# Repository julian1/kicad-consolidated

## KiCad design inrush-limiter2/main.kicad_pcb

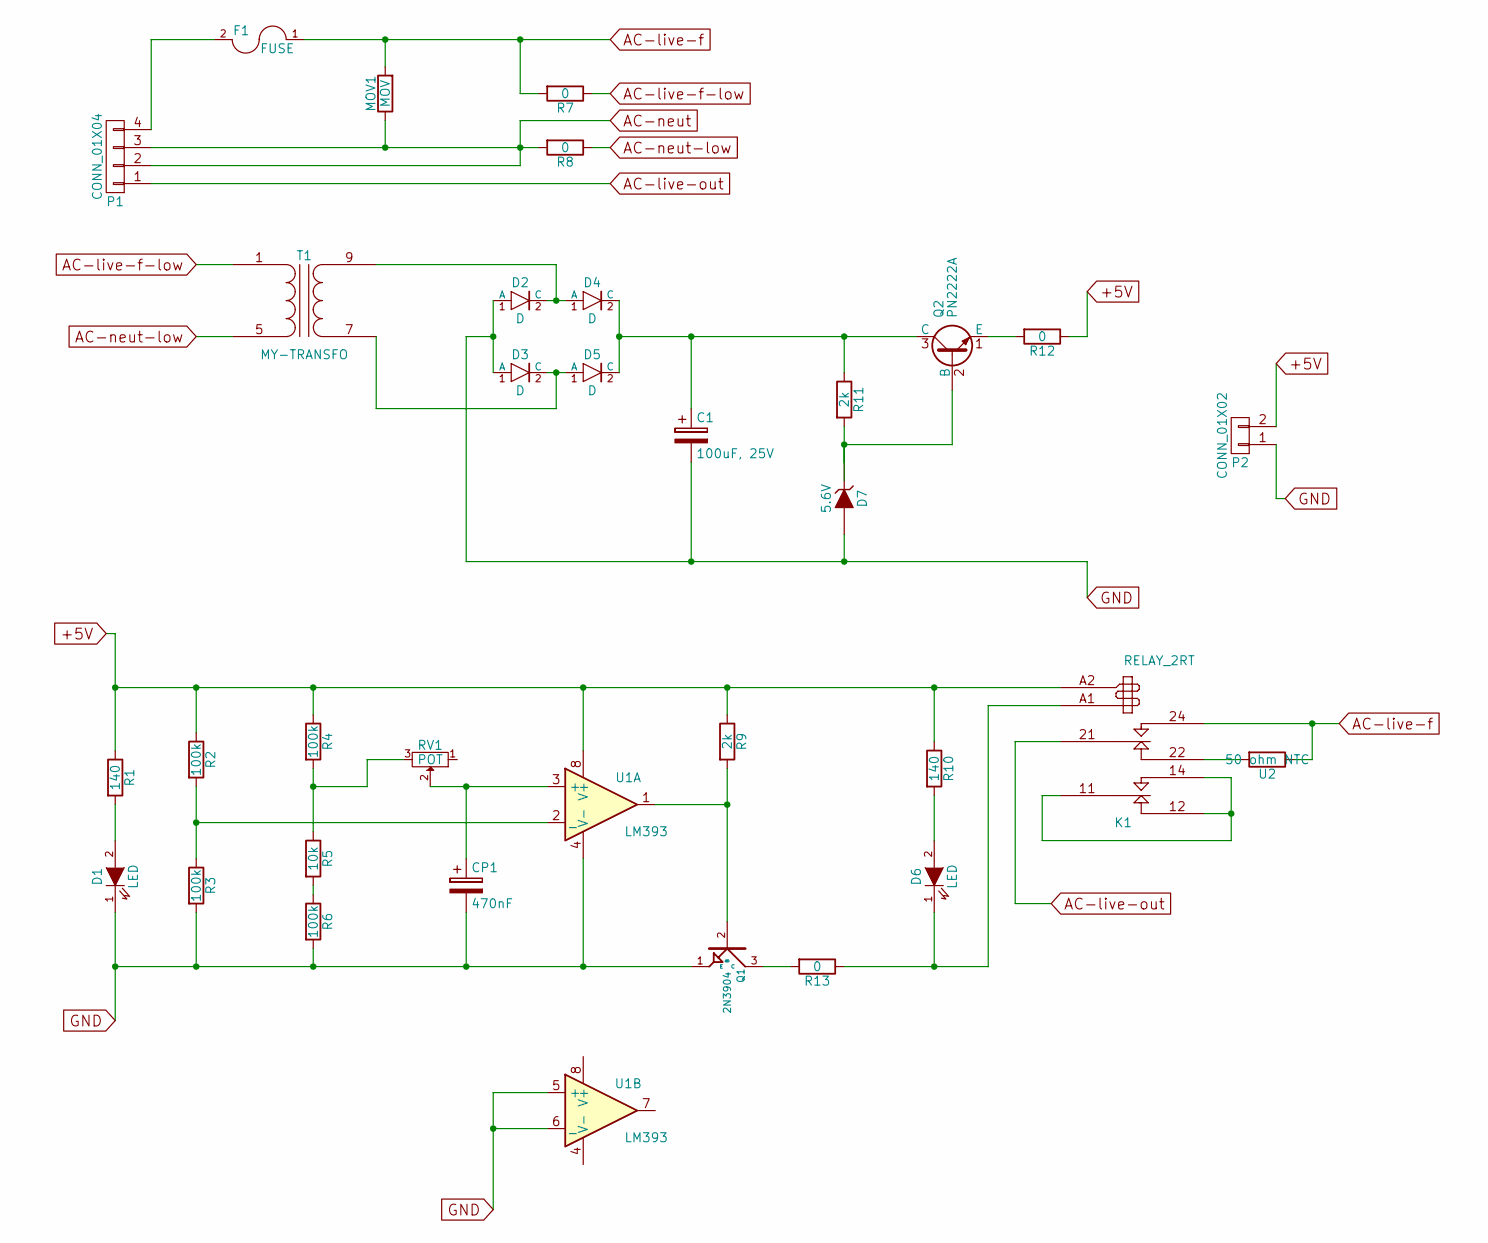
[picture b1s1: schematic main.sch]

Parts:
C1: 100uF, 25V; C_Radial_D8_L13_P3.8
CP1: 470nF; C_Rect_L7_W3.5_P5
D1, D6: LED; LED-5MM
D2, D3, D4, D5: D; Diode_DO-35_SOD27_Horizontal_RM10
D7: 5.6V; Diode_DO-35_SOD27_Horizontal_RM10
F1: FUSE; Fuseholder5x20_horiz_SemiClosed_Casing10x25mm
K1: RELAY_2RT; Relay_DPDT_Schrack-RT2_RM5mm
MOV1: MOV; Resistor_Horizontal_RM10mm
P1: CONN_01X04; fuck
P2: CONN_01X02; Pin_Header_Straight_1x02
Q1: 2N3904; TO-92_Inline_Wide
Q2: PN2222A; TO-92_Inline_Wide
R1, R10: 140; Resistor_Horizontal_RM7mm
R2, R3, R4, R6: 100k; Resistor_Horizontal_RM7mm
R5: 10k; Resistor_Horizontal_RM7mm
R7, R8, R12, R13: 0; Resistor_Horizontal_RM7mm
R9, R11: 2k; Resistor_Horizontal_RM7mm
RV1: POT; Potentiometer_Bourns_3296W_3-8Zoll_Inline_ScrewUp
T1: MY-TRANSFO; my-transformer
U1: LM393; DIP-8_W7.62mm
U2: 50 ohm NTC; Resistor_Horizontal_RM10mm

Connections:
+5V: K1.A2 (9), P2.2, R1.1, R2.1, R4.1, R9.1, R10.1, R12.1, U1.8 (V+)
AC-live-f: F1.1, K1.24 (T1), MOV1.2, R7.2, U2.1
AC-live-f-low: R7.1, T1.1 (AA)
AC-live-out: K1.21 (C1), P1.1
AC-neut: MOV1.1, P1.2, P1.3, R8.2
AC-neut-low: R8.1, T1.5 (AB)
GND: C1.2, CP1.2, D1.1 (K), D2.1 (A), D3.1 (A), D7.2 (A), P2.1, Q1.1 (E), R3.2, R6.2, U1.4 (V-), U1.5 (+), U1.6 (_)
unnamed: C1.1, D4.2 (C), D5.2 (C), Q2.3 (C), R11.1
unnamed: CP1.1, RV1.2, U1.3 (+)
unnamed: D1.2 (A), R1.2
unnamed: D2.2 (C), D4.1 (A), T1.9 (SB)
unnamed: D3.2 (C), D5.1 (A), T1.7 (SA)
unnamed: D6.1 (K), K1.A1 (8), R13.1
unnamed: D6.2 (A), R10.2
unnamed: D7.1 (K), Q2.2 (B), R11.2
unnamed: F1.2, P1.4
unnamed: K1.11 (C2), K1.12, K1.14 (T2)
unnamed: K1.22 (R1), U2.2
unnamed: Q1.2 (B), R9.2, U1.1
unnamed: Q1.3 (C), R13.2
unnamed: Q2.1 (E), R12.2
unnamed: R2.2, R3.1, U1.2 (_)
unnamed: R4.2, R5.1, RV1.3
unnamed: R5.2, R6.1

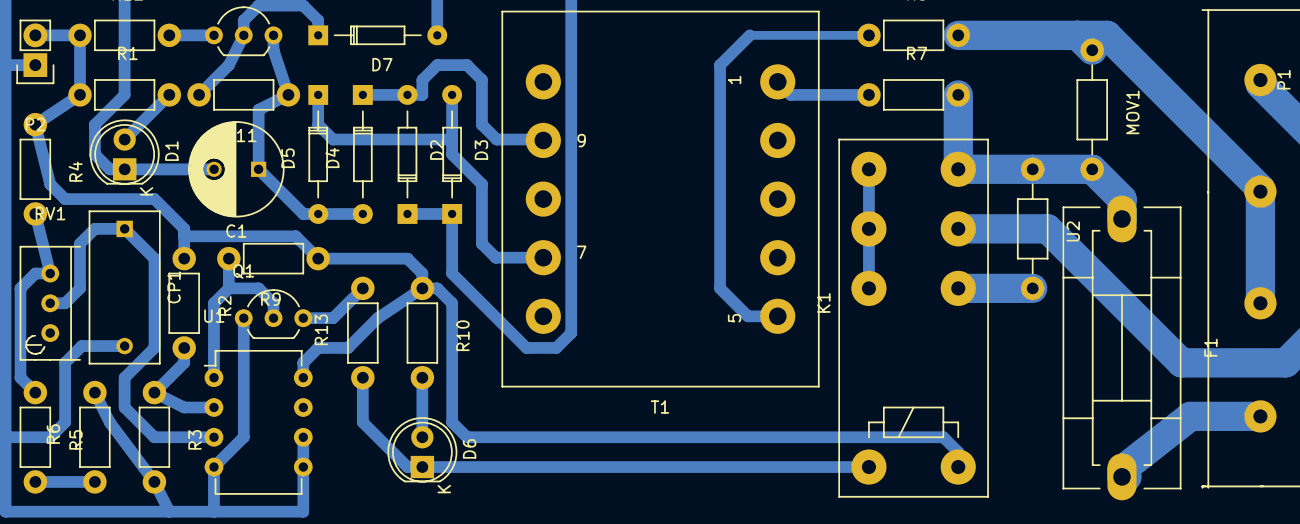
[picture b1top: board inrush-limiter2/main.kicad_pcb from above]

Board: 2 copper layers, 33 parts (0 on the bottom side), 24 nets.

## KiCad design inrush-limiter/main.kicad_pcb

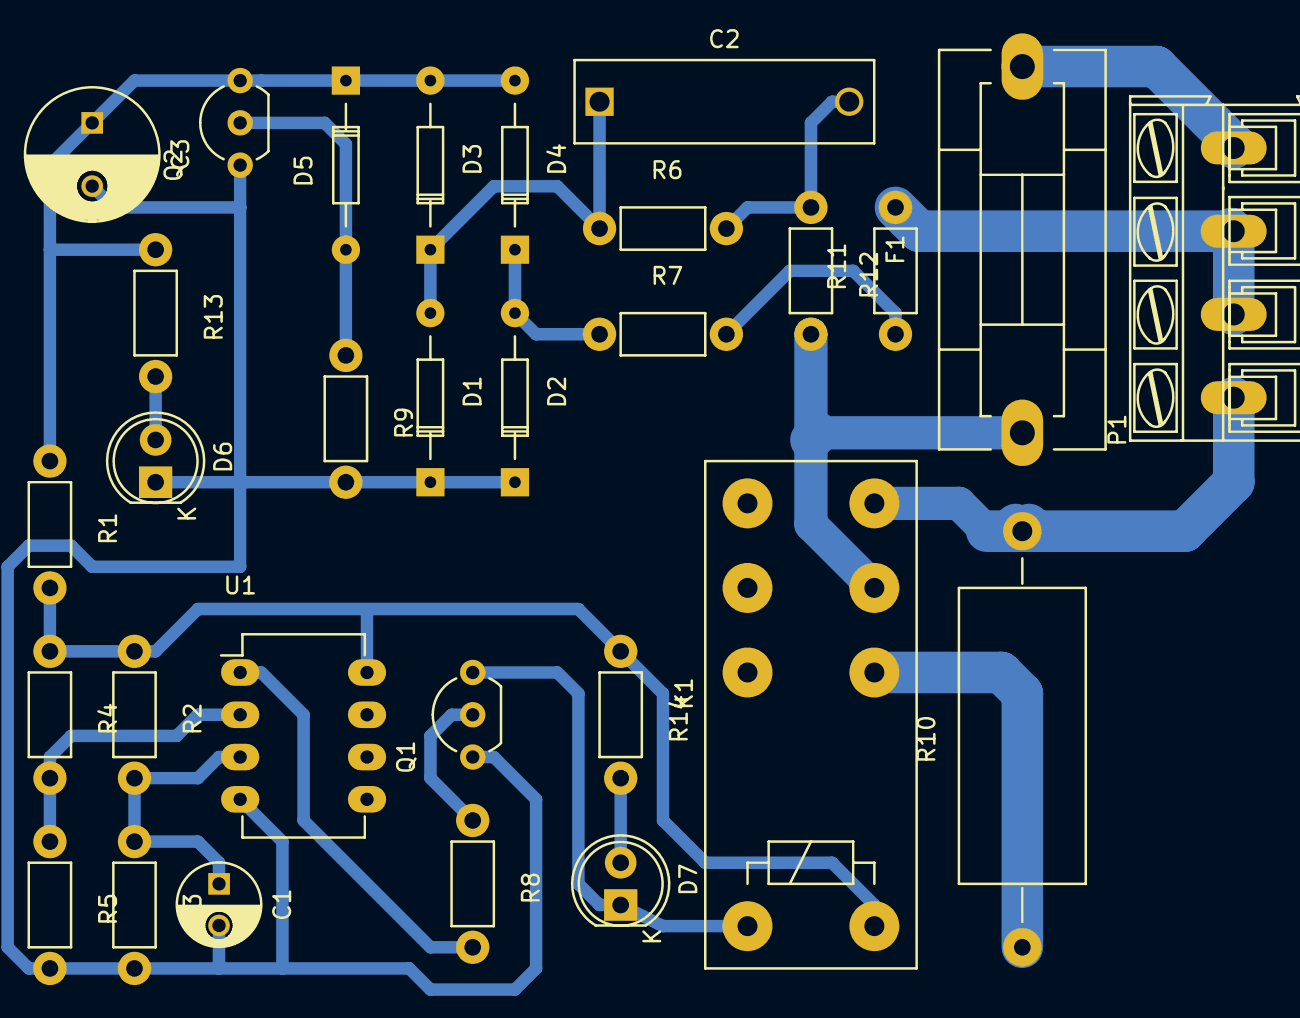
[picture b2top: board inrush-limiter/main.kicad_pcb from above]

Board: 2 copper layers, 30 parts (0 on the bottom side), 20 nets.

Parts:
C1: 3.3uF; C_Radial_D5_L6_P2.5
C2: 47nF, x2; C_Rect_L18_W5_P15
C3: 100uF, 25V; C_Radial_D8_L13_P3.8
D1, D2, D3, D4: D; Diode_DO-35_SOD27_Horizontal_RM10
D5: ZENER; Diode_DO-35_SOD27_Horizontal_RM10
D6, D7: LED; LED-5MM
F1: FUSE; Fuseholder5x20_horiz_SemiClosed_Casing10x25mm
K1: RELAY_2RT; Relay_DPDT_Schrack-RT2_RM5mm
P1: CONN_01X04; AK300-4
Q1, Q2: PN2222A; TO-92_Inline_Wide
R1, R11, R12: 0; Resistor_Horizontal_RM7mm
R2: 100K; Resistor_Horizontal_RM7mm
R3: 1M; Resistor_Horizontal_RM7mm
R4: 10K; Resistor_Horizontal_RM7mm
R5: 50K; Resistor_Horizontal_RM7mm
R6: 470k; Resistor_Horizontal_RM7mm
R7: 100; Resistor_Horizontal_RM7mm
R8: 1K; Resistor_Horizontal_RM7mm
R9: 2k; Resistor_Horizontal_RM7mm
R10: 100, 5W; Resistor_Horizontal_RM25mm
R13, R14: 140; Resistor_Horizontal_RM7mm
U1: LM393; DIP-8_W7.62mm_LongPads

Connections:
+5V: C3.1, D3.2, D4.2, D5.1, Q2.3, R1.1, R13.1
AC-live-f: F1.1, K1.21, R12.2
AC-live-f-low: C2.2, R6.2, R12.1
AC-live-out: K1.24, P1.1, R10.2
AC-neut: P1.2, P1.3, R11.2
AC-neut-low: R7.2, R11.1
GND: C1.2, C3.2, D1.1, D2.1, D6.1, Q1.1, Q2.1, R3.2, R5.2, R9.2, U1.4
unnamed: C1.1, R2.2, R3.1, U1.3
unnamed: C2.1, D1.2, D3.1, R6.1
unnamed: D2.2, D4.1, R7.1
unnamed: D5.2, Q2.2, R9.1
unnamed: D6.2, R13.2
unnamed: D7.1, K1.A1, Q1.3
unnamed: D7.2, R14.2
unnamed: F1.2, P1.4
unnamed: K1.22, R10.1
unnamed: K1.A2, R1.2, R2.1, R4.1, R14.1, U1.8
unnamed: Q1.2, R8.1
unnamed: R4.2, R5.1, U1.2
unnamed: R8.2, U1.1

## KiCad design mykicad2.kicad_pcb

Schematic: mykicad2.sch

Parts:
D1, D2: 1N4148; MiniMELF_Standard
P1: CONN_01X06; Pin_Header_Straight_1x06
Q1: MMBT3904; SOT-23
Q2: MMBT3906; SOT-23
Q3: IRF9540N; TO-220
R1, R2, R3, R4, R5: R; R_1206

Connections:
GND: P1.2, Q2.3, R2.2
unnamed: D1.1, Q1.1, R1.2
unnamed: D1.2, D2.1, P1.3
unnamed: D2.2, Q2.1, R2.1
unnamed: P1.4, Q3.3
unnamed: Q1.2, R3.1
unnamed: Q2.2, R4.2
unnamed: Q3.1, R5.1
unnamed: R3.2, R4.1, R5.2
VDD: P1.1, Q1.3, Q3.2, R1.1

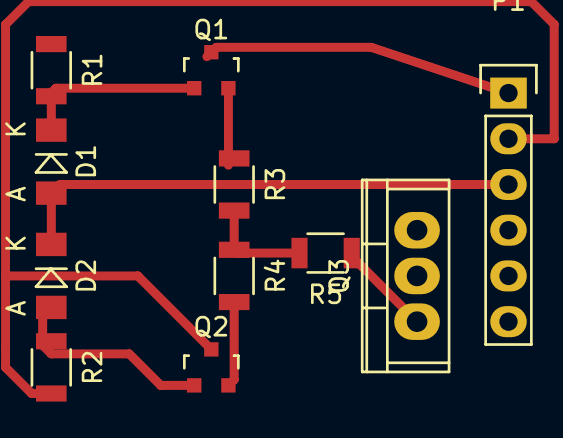
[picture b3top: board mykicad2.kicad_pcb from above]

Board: 2 copper layers, 11 parts (0 on the bottom side), 10 nets.

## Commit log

2016-08-13 orientate components
2016-08-13 vertical header pins
2016-08-13 added traces
2016-08-13 added fill
2016-08-13 fix trace
2016-08-13 improve traces
2016-08-13 big current
2016-08-13 relayout with mosfet
2016-08-14 add mosfet update traces
2016-08-26 move mosfet to separate example
2016-08-26 inrush initial
2016-08-27 looks ok
2016-08-27 add isolation resistor
2016-08-27 tidy
2016-08-27 start of pcb
2016-08-27 half-laid out
2016-08-27 fix relay footprint and reimport
2016-08-27 got track width separated by netlist using 0 resistor
2016-08-27 add gnd plane
2016-08-27 with fills
2016-08-27 set clearances to 0.75mm
2016-08-27 .25 trace and space
2016-08-27 .5 trace and 1mm clearance
2016-08-27 .5 trace and 1.25mm clearance
2016-08-27 fix connections
2016-08-27 add leds
2016-08-28 added high-clearance low current traces
2016-08-28 fix missing 5v supply
2016-08-28 update todo
2016-09-04 inrush 2
2016-09-06 update and add cache files
2016-09-06 fix up annotation
2016-09-06 update net
2016-09-06 adjust component positions
2016-09-07 use pot
2016-09-07 add custom footprint for terminal block
2016-09-07 increase pad size
2016-09-07 update terminal block outline
2016-09-07 fix terminal block outline
2016-09-07 add pin headers
2016-09-07 add todo
2016-09-07 add new transformer schematic and footprint
2016-09-07 tidying
2016-09-07 more tidying
2016-09-07 update, problem with transistor to ground
2016-09-07 fixed with a resistor but not sure its necessary
2016-09-07 yes its needed
2016-09-07 good
2016-09-08 fix capacitor and tidying
2017-02-18 rename inrush
